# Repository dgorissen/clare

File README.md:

# C.L.A.R.E - Come Look At Robot Entertainment

CLARE, short for Come Look At Robot Entertainment, is an interactive robot I designed together with the kids and have been working on (and still am) for quite some time. Its mostly for fun and to expose the kids to robotics but also allows me to scratch that technical itch as my professional life ventures into documents, spreadsheets, powerpoint, and meetings.

I am designing CLARE fully from scratch, including all CAD, wiring, coding, custom PCBs, etc. Printing happens on my home 3D printer. CLARE features multiple cameras, face recognition and tracking, interactive voice commands, LCD screen, LEDs, and fart detector. It can be controlled with an RC remote or (planned) move autonomously using SLAM.

This is still a work in progress and updates will come whenever I find a pocket of time.

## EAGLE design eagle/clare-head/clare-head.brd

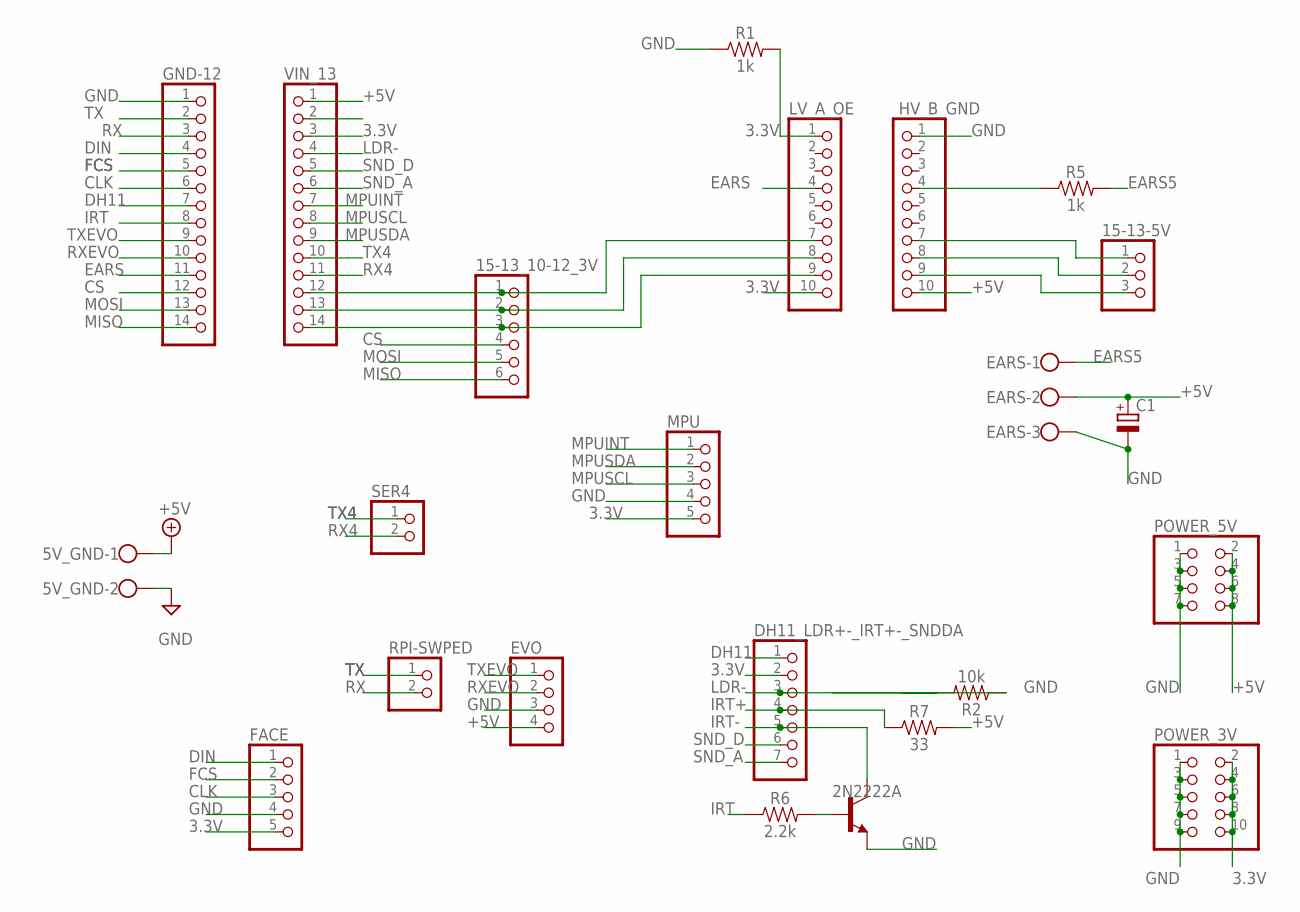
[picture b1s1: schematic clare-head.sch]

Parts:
2N2222A: 2N2222A-NPN-TO18-EBC; TO18
5V_GND: W237-102
15-13-5V: PINHD-1X3; 1X03
15-13_10-12_3V: PINHD-1X6; 1X06
C1: CPOL-EUE2,5-6E; E2,5-6E
DH11_LDR+-_IRT+-_SNDDA: PINHD-1X7; 1X07
EARS: W237-103
EVO: PINHD-1X4; 1X04
FACE: PINHD-1X5; 1X05
GND-12: PINHD-1X14; 1X14
HV_B_GND: PINHD-1X10; 1X10
LV_A_OE: PINHD-1X10; 1X10
MPU: PINHD-1X5; 1X05
POWER_3V: PINHD-2X5; 2X05
POWER_5V: PINHD-2X4; 2X04
R1, R5: 1k; AXIAL-0.3
R2: 10k; AXIAL-0.3
R6: 2.2k; AXIAL-0.3
R7: 33; AXIAL-0.3
RPI-SWPED: PINHD-1X2; 1X02
SER4: PINHD-1X2; 1X02
VIN_13: PINHD-1X14; 1X14

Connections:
3.3V: DH11_LDR+-_IRT+-_SNDDA.2, FACE.5, LV_A_OE.1, LV_A_OE.10, MPU.5, POWER_3V.2, POWER_3V.4, POWER_3V.6, POWER_3V.8, POWER_3V.10, R1.P$2 (2), VIN_13.3
+5V: 5V_GND.1, C1.+, EARS.2, EVO.4, HV_B_GND.10, POWER_5V.2, POWER_5V.4, POWER_5V.6, POWER_5V.8, R7.P$2 (2), VIN_13.1
CLK: FACE.3, GND-12.6
CS: 15-13_10-12_3V.4, GND-12.12
DH11: DH11_LDR+-_IRT+-_SNDDA.1, GND-12.7
DIN: FACE.1, GND-12.4
EARS: GND-12.11, LV_A_OE.4
EARS5: EARS.1, R5.P$2 (2)
FCS: FACE.2, GND-12.5
GND: 2N2222A.1 (E), 5V_GND.2, C1.-, EARS.3, EVO.3, FACE.4, GND-12.1, HV_B_GND.1, MPU.4, POWER_3V.1, POWER_3V.3, POWER_3V.5, POWER_3V.7, POWER_3V.9, POWER_5V.1, POWER_5V.3, POWER_5V.5, POWER_5V.7, R1.P$1 (1), R2.P$1 (1)
IRT: GND-12.8, R6.P$1 (1)
IRT+: DH11_LDR+-_IRT+-_SNDDA.4, R7.P$1 (1)
IRT-: 2N2222A.3 (C), DH11_LDR+-_IRT+-_SNDDA.5
LDR-: DH11_LDR+-_IRT+-_SNDDA.3, R2.P$2 (2), VIN_13.4
MISO: 15-13_10-12_3V.6, GND-12.14
MOSI: 15-13_10-12_3V.5, GND-12.13
MPUINT: MPU.1, VIN_13.7
MPUSCL: MPU.3, VIN_13.8
MPUSDA: MPU.2, VIN_13.9
unnamed: 2N2222A.2 (B), R6.P$2 (2)
unnamed: 15-13-5V.1, HV_B_GND.7
unnamed: HV_B_GND.4, R5.P$1 (1)
unnamed: 15-13-5V.2, HV_B_GND.8
unnamed: 15-13-5V.3, HV_B_GND.9
unnamed: 15-13_10-12_3V.1, LV_A_OE.7, VIN_13.12
unnamed: 15-13_10-12_3V.2, LV_A_OE.8, VIN_13.13
unnamed: 15-13_10-12_3V.3, LV_A_OE.9, VIN_13.14
RX: GND-12.3, RPI-SWPED.2
RX4: SER4.2, VIN_13.11
RXEVO: EVO.2, GND-12.10
SND_A: DH11_LDR+-_IRT+-_SNDDA.7, VIN_13.6
SND_D: DH11_LDR+-_IRT+-_SNDDA.6, VIN_13.5
TX: GND-12.2, RPI-SWPED.1
TX4: SER4.1, VIN_13.10
TXEVO: EVO.1, GND-12.9

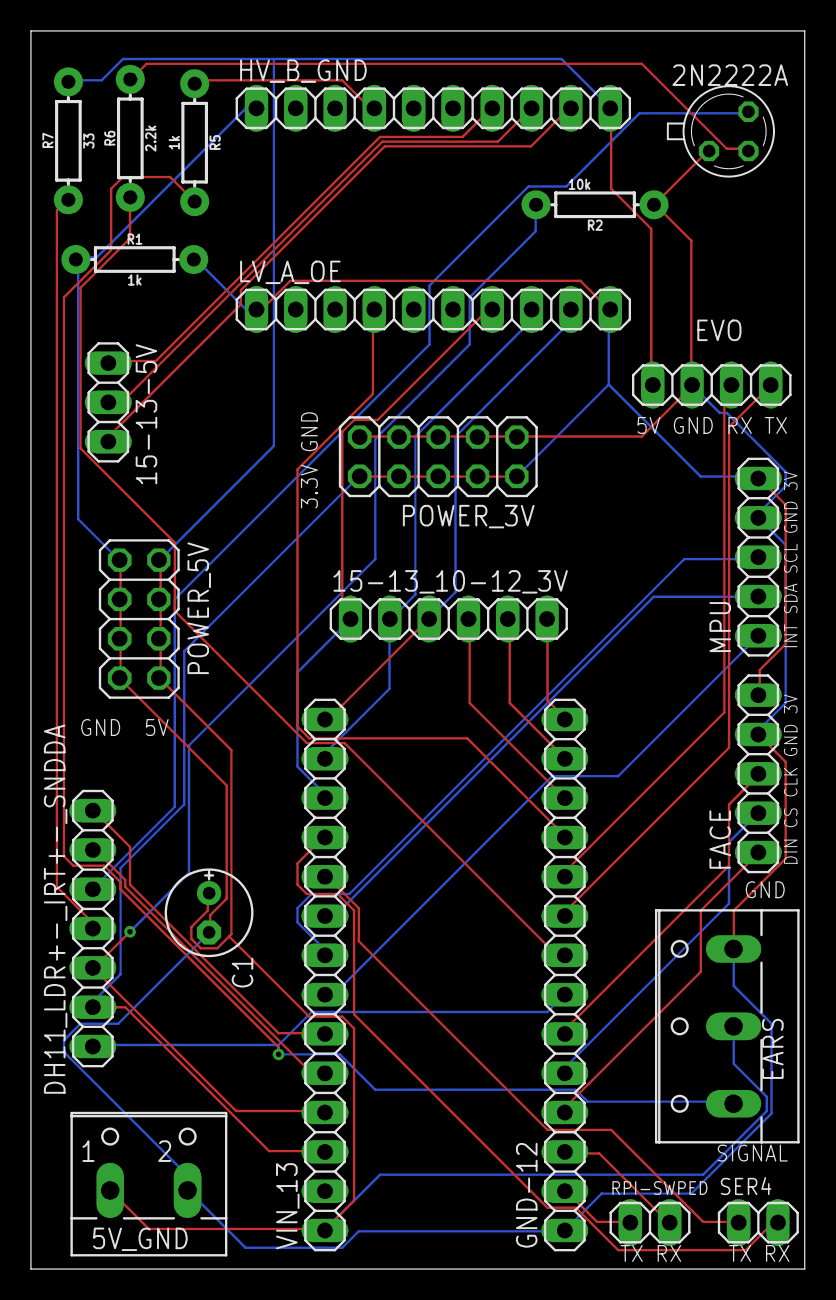
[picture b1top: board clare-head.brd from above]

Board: 2 copper layers, 50.0 x 80.0 mm, 23 parts (0 on the bottom side), 35 nets.

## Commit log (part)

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2020-03-15 Basic facial expressions working
2021-01-10 - Move head files into subdirectory - Add tracks subdirectory - Got tracks to work on robot (manual differential control with RC) - Refactored / cleaned up tracks, not tested yet on robot
2021-01-11 Add util function
2021-01-11 Update comments
2021-01-11 Code cleanup & refactor
2021-01-14 Handle reversing a bit more intuitively
2021-02-20 As run on the first RC session
2021-02-20 Fix reverse steering issue (was hitting exactly 0 on <0 check)
2021-03-14 Update bootstrap
2021-03-14 Update docker commands to fit hub repo
2021-03-16 Working docker up to cv2.__version__
2021-03-21 Install x2go, setup ssh, start flask hello world
2021-03-21 Scaffolding connecting flask and vue app based of template. Seems to work
2021-04-04 Switch to ROS1 in dockerfile, setup everything for simple end-2-end test where browser call can control headlights. not tested on robot yet
2021-04-04 Fix typo
2021-04-04 Various fixes as part of testing on pi, not quite there yet
2021-04-04 More tweaks as part of testing
2021-04-04 Better arch detect
2021-04-04 Add clean target
2021-04-04 Verbose pyenv install
2021-04-04 Add missing self params
2021-04-04 Use ~ instead of abs path
2021-04-04 Give roscore some time to start
2021-04-13 As successsfully built and run (cbrain container)
2021-04-13 Add BAUD variable
2021-04-13 Dont ignore lib
2021-04-13 First pass of formally pubhlishing a state object over ros. Not tested on robot yet.
2021-04-14 Fix wrong channel assignment, changed state serialisation to String Successful end-2-end headlights control from REST call, through ROS
2021-04-15 Remember to always spinOnce
2021-04-15 Cleaner mode setting in output state
2021-04-15 No need for safestring
2021-04-15 Change headlight message to match teensy changes
2021-04-15 Add not connected check
2021-04-16 Cleanup of webapp, now single card for Tracks with some basic functions Tested locally, not yet on robot
2021-04-16 End-2-end card-robot tested and works!
2021-04-16 Set page title
2021-04-18 Working NCS2 in docker and web frontend / ros comms
2021-04-18 ros export vars are needed for master, not rosserial
2021-04-18 Reduce roscore waittime to 3s
2021-05-03 Add support for realsense, adafruit sound bonnet, respeaker, piwatcher Docker builds, just needs cleanup
2021-05-03 Cleanup dockerfile + update boostrap
2021-06-23 Add x11-apps
2021-06-23 Add ultrasound reading code for xiao
2021-07-13 Add NCS test
2021-07-13 Bump versions, update / fix pyenv working on librealsense
2021-07-13 Set correct usb for tracks
2021-07-21 Added body middle eagle files as submitted to allpcb
2021-07-21 Working realsense
2021-08-07 Use ip instead of localhost for ros master uri
2021-08-07 Add comment to install missing package
2021-08-07 Add timeout to clare_body_middle.py and dont immediately fail on float conversion
2021-08-07 Log float conversion error to ros
2021-08-07 No need for track port variables as /dev is mounted
2021-08-07 Log before starting each command, put sleeps in between, and tail rosout
2021-08-08 Cleaned up tracks a bit, added middle, not tested yet
2021-08-08 Put connected guard on /connect
2021-08-08 Set connected status correctly on page load
2021-08-08 Add working card for middle
2021-08-09 Increase time waiting for roscore to start
2021-08-20 Set default python interpreter in workspace
2021-08-28 Moved code for eyes into separate folder
2021-08-28 Start thinking about face detection on camera stream, initial untested snippets
2021-08-29 Cant pip install opengl
2021-09-04 Make x fwding work from inside docker container
2021-09-04 Add head folder to workspace
2021-09-04 Make openvino movidius test command work on copy paste
2021-09-04 Remove non existant mssage file
2021-09-04 Move eyes out of head to top level clare folder
2021-09-04 Fix grammar
2021-09-04 Face detect node now actually starts a node & publishing channel
2021-09-05 Make face detection work with AsyncPipeline, with 2 output topics, tested
2021-09-05 Update Dockerfile, plain output when building
2021-09-06 Reorg dockerfile as part of debugging layer not caching issue. All works now. Also removed unused targets from Makefile
2021-09-06 Start head camera feed in entrypoint, resolved cv2 issue in entrypoint
2021-09-12 Add respeaker rules info
2021-09-12 Update dockerfile with respeaker/ros stuff
2021-09-12 Add TTS tools
2021-09-15 Add respeaker & TTS pkgs and nodes
2021-09-15 First wiring up of TTS and STT with web ui, not tested
2021-09-18 Speak to me button works
2021-09-18 Add flag to start just container & rosmaster
2021-09-19 Run respeaker notes from jsk catking package
2021-09-19 STT nodes should now work
2021-09-19 Fix wrong stream name in client and just return top transcript in app
2021-09-19 Scroll to bottom needs to happen at each update
2021-09-19 Store cmd in variable
2021-09-19 Update/re-org Dockerfile
2021-09-25 Also start realsense node in entrypoint
2021-09-25 Add missing state.py
2021-09-25 Working depth feed
2021-09-25 Add depth view to web page, works
2021-09-26 Teensy tracks code changes to receive driving commands over ROS, not tested yet
2021-10-18 Remove alsa card preference from bashrc after removal of sound bonnet
2021-10-20 Web joystick control roughly works but still jerky
2021-11-07 Set output card in tts
2021-11-07 Start ros node in own thread
2021-12-10 Basic code in place for testing top sensors. Not tested yet.
2021-12-11 Add adafruit libs
2021-12-13 Working way through issues
2021-12-14 Update docker & bootstrap files as part of getting top working
2021-12-15 Mount /sys/class/gpio just in case
2021-12-15 Further debugging, servos work now
2021-12-15 Expose environmentals
2021-12-18 Button node woks now
2021-12-18 Node doesnt ignore signals and set node name
2021-12-18 Working ir node
2021-12-19 Add working launch file
2021-12-19 Middle node follows the same structure as the others. Ensure msg dirs exist
2021-12-19 Bring head camera node in line with other nodes
2021-12-19 split ros_pkgs into ros_build and ros_install targets
2021-12-19 Use launch file for ros nodes
2021-12-19 Ensure jsk_3rdparty respeaker_ros is installed
2021-12-19 Fix wrong channel name
2021-12-19 Use consistent naming for head camera node
2021-12-19 Ensure ctrl-c shuts down node
2021-12-20 openvino environment needs to be sourced before running backend (for python libs)
2021-12-30 First versions of remaining body top nodes, not tested yet
2022-01-03 Fix catkin build and running of new nodes
2022-01-03 Enable passwordless sudo
2022-01-03 Flask api for new nodes works
2022-01-03 Moved ros pub/sub inside states. Unmute by default
2022-01-03 Add makefile commands to build/upload tracks/teensy
2022-01-03 Add tracks makefile
2022-01-03 Setup environment once for all tasks in entrypoint
2022-01-03 Add placeholder top.png file
2022-01-03 Quick support of new nodes in web ui, mostly works
2022-01-03 Support returning top state
2022-01-04 Set initial lightring value
2022-01-04 Add off value
2022-01-04 remove photo stuff
2022-01-04 Cleanup gpio on exit
2022-01-04 Reorder top card
2022-01-04 Rosify ultrasound project and refactor into clare_middle. Not tested yet.
2022-01-04 Add msg files
2022-01-04 compilation/upload plumbing of middle now works but doesnt succeed yet..
2022-01-05 Ros and arduino nano dont play well together, reverted back to serial
2022-01-05 Middle node fully working again
2022-01-05 Add arduino libs
2022-01-05 Remove unused printvals
2022-01-05 Update backend to new middle node
2022-01-05 Refactor tracks into into a better ros_node, not tested yet
2022-01-05 Fix compilation
2022-01-05 TX SE switch allows for manually overriding any sw commands
2022-01-05 Publish motor direction and only publish if changed
2022-01-05 Swap left/right encoder to match hardware, remove unused publish fcns
2022-01-05 Update webapp to new tracks topics
2022-01-05 Warning instead of exception on unknown entry
2022-01-05 Use .data on ros msgs
2022-01-06 Fix logging call
2022-01-06 Allow passing of arguments to the entrypoint
2022-01-07 Use SPI for light ring to avoid clash with audio
2022-01-07 Lightring moved to spi, USB devices have changed, get everything running again
2022-01-07 Move boot config into config dir
2022-01-10 USB devices changed. All components verified working
2022-01-11 Refactored directory structure. Squashed commit of the following:
    commit 9d2af2d57dc403af1e15bddf754a8289719a1de0
    Author: Dirk Gorissen <dgorissen@gmail.com>
    Date: Tue Jan 11 11:40:29 2022 +0000
    Update bootstrap
    commit 829977e8ce4b97d7247a4427f487556ecb65e4f0
    Author: Dirk Gorissen <dgorissen@gmail.com>
2022-01-12 Add missing flac library
2022-01-14 Bump base docker image version and other key versions. All works.
2022-01-17 Add neck node folder
2022-01-18 Fix vue model name
2022-01-18 Update neck limits after testing in robot
2022-01-20 TTS now in separate node and uses gtts by default
2022-01-20 Update dockerfile to suppport new tts node
2022-01-22 Tighten range of motion left/right for neck
2022-01-29 Now able to control all arm servos from the webapp
2022-01-29 Update arms picture
2022-01-29 Add extra pkgs
2022-04-16 Update arm servo ranges
2022-04-17 Refactor arm control (not tested yet)
    - use ServoJoint wrapper class
    - track current position
    - allow reset to home
2022-04-17 Rename arm_servos to arm_joints
2022-04-17 Refactor eyes folder ready for rosification
2022-04-17 Add Makefile & pio config
2022-04-17 Add more scaffolding files
2022-04-29 Add cmakelists
2022-04-29 Fix most compile errors
2022-05-01 Fix face compilation
2022-05-01 Updated expressions to fit head configuration and added many more
2022-05-15 Clare head PCB design as per first manufacture
2022-05-22 First code for testing/flushing clare's head
2022-05-23 Comment out ros stuff
2022-05-23 Update pin numbers
2022-05-30 Head pcb v2 submitted for manufacture
2022-06-21 Add gitignore
2022-06-21 add gui-docker script
2022-07-03 Fix reading and printing of evo mini
2022-07-30 Cleanups as part of testing new pcb
2022-08-02 Head pcb works and tested. Ready for head assembly
2022-08-03 Update IP address
2022-08-08 Reduce number of files vscode is watching
2022-08-08 Set upload port to avoid confusion between teensys
2022-08-08 Add note to set /etc/host
2022-08-08 Use hostname instead of ip
2022-08-10 Parameterise docker tag
2022-08-10 Remove quotes
2022-08-11 Fix compilation issues in tracks which somehow were still there...
2022-08-11 All compiles but failing to test due to weird teensy usb port swapping/clash issue
2022-08-12 Use tytools for teensy upload to workaround pio bug
2022-08-12 Head node publishing works
2022-08-12 Move loop expressions into face
2022-08-14 Temp commit
2022-08-14 Service for returning available face expressions works
2022-08-14 Reduce lag on evo publishing
2022-08-14 Update service name
2022-08-14 Flesh out ir message
2022-08-14 Check timestamps before yielding jpeg img in stream
2022-08-15 Fix compilation issues
2022-08-17 Fix starting of npm serve and update packages
2022-08-17 Set API endpoint back to ip
2022-08-17 Fix issues
2022-08-17 Fix bugs
2022-08-17 Fix use of wrong publisher
2022-08-17 Add user to plugdev
2022-08-17 Fix face expression dropdown
2022-08-18 Resize all images to fixed size
2022-09-03 Add controller node stub
2022-09-05 Add python libs
2022-09-05 Basic controller, not tested yet
2022-09-05 Some fixes, not working yet
2022-09-06 Extended & refactored controller somewhat, works
2022-09-06 Small tweaks
2022-09-10 Use webcolors for lightring
2022-09-10 Add insulted state
2022-09-10 Fix event name
2022-09-11 Tweak insulted
2022-09-27 Add some idle behavior
2022-10-01 Parallel servo moving works, added love state
2023-01-02 Add imgview node
2023-09-09 Use ChatGPT for non-pre-cooked responses, not tested yet
2023-09-09 Add openai dependency
2023-09-09 Put guard on noise handler
2023-09-09 Fix dict attr acces
2023-09-26 Update Dockerfile to build again
2023-10-28 Change local ip setting, set ros_hostname
2023-10-28 Fix imgview node

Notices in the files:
parts and their libraries:
SparkFun-Resistors: Licensing: Creative Commons ShareAlike 4.0 International - https://creativecommons.org/licenses/by-sa/4.0
